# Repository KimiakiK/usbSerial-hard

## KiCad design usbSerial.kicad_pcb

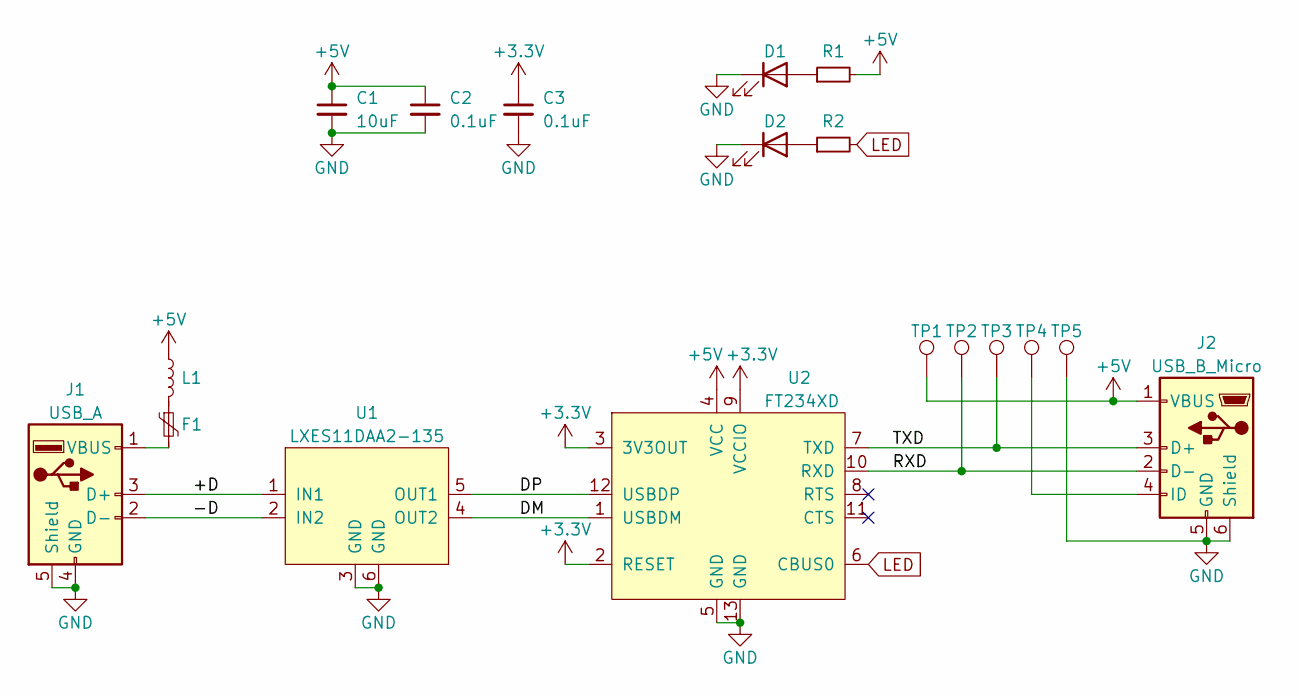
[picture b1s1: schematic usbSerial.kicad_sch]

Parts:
C1: 10uF; 1608Metric
C2, C3: 0.1uF; 1608Metric
D1, D2: LED; 1608Metric
F1: Polyfuse; 1608Metric
J1: USB_A; USB Type-A
J2: USB_B_Micro; USB MicroB ZX62-B-5PA
L1: L; 1608Metric
R1, R2: R; 1608Metric
TP1, TP2, TP3, TP4, TP5: TestPoint; TestPoint_THTPad_D1.5mm_Drill0.9mm
U1: LXES11DAA2-135; LXES11D
U2: FT234XD; DFN-12-1EP_3x3mm_P0.45mm_EP1.66x2.38mm

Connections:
+3.3V: C3.1, U2.2 (RESET), U2.3 (3V3OUT), U2.9 (VCCIO)
+5V: C1.1, C2.1, J2.1 (VBUS), L1.1, R1.2, TP1.1, U2.4 (VCC)
/+D: J1.3 (D+), U1.1 (IN1)
/-D: J1.2 (D-), U1.2 (IN2)
/DM: U1.4 (OUT2), U2.1 (USBDM)
/DP: U1.5 (OUT1), U2.12 (USBDP)
/RXD: J2.2 (D-), TP2.1, U2.10 (RXD)
/TXD: J2.3 (D+), TP3.1, U2.7 (TXD)
GND: C1.2, C2.2, C3.2, D1.1 (K), D2.1 (K), J1.4 (GND), J1.5 (Shield), J2.5 (GND), J2.6 (Shield), TP5.1, U1.3 (GND), U1.6 (GND), U2.5 (GND), U2.13 (GND)
LED: R2.2, U2.6 (CBUS0)
unnamed: D1.2 (A), R1.1
unnamed: D2.2 (A), R2.1
unnamed: F1.1, L1.2
unnamed: F1.2, J1.1 (VBUS)
unnamed: J2.4 (ID), TP4.1

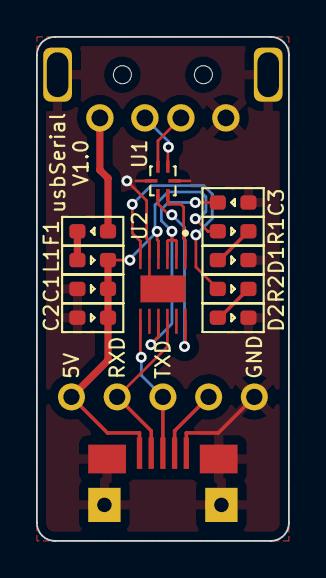
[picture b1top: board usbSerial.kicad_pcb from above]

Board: 2 copper layers, 14.0 x 28.0 mm, 18 parts (1 on the bottom side), 15 nets.

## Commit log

2022-11-13 基板V1.0
2022-11-14 ドリル穴径修正(0.2mm -> 0.3mm)
